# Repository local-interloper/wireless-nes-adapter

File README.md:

# Wireless NES Adapter

The goal of this project was to design a piece of hardware that you can use to play computer games 
using the original Nintendo Entertainment System controller. It comes with all the code, PCB 
schematics and information required to get a printed circuit board printed and assemble and 
program the hardware.

## Requirements

- [KiCad](https://www.kicad.org/)
- esp32-s3 devboard (make sure it looks like [this](https://docs.espressif.com/projects/esp-dev-kits/en/latest/esp32s3/_images/esp32-s3-devkitc-1-v1.1-isometric.png))
- NES Controller socket (easily found on AliExpress)
- Arduino IDE setup with [`arduino-esp32`](https://github.com/espressif/arduino-esp32) and [`ESP32-BLE-Gamepad`](https://github.com/lemmingDev/ESP32-BLE-Gamepad) installed
- A soldering iron and some solder

## How to build

1. Select a PCB printing service of your choice (I went with [Aisler](https://aisler.net/en-US)).
2. If your PCB printing service does not support native KiCad files, open `kicad/wireless-nes-adapter` 
    in KiCad and export the schematics so you can get your PCB printed.
3. Assemble the hardware.
4. With your Arduino IDE set up with the aforementioned libraries, select the ESP32-S3 as the target and flash 
    `/arduino/wireless-nes-adapter.ino` to the board.
5. Plug in your controller and power the board via USB.
6. Add the controller in your computer's bluetooth devices.

## All set!

You should now be all set. I recommend using steam as steam input allows you to use the direct input controller
you've just built as an xinput one via remapping. I recommend testing the controller on 
[Rain World](https://store.steampowered.com/app/312520/Rain_World/) or [Celeste](https://store.steampowered.com/app/504230/Celeste/) 
if you have any of those 2 titles due to their low input count requirement.

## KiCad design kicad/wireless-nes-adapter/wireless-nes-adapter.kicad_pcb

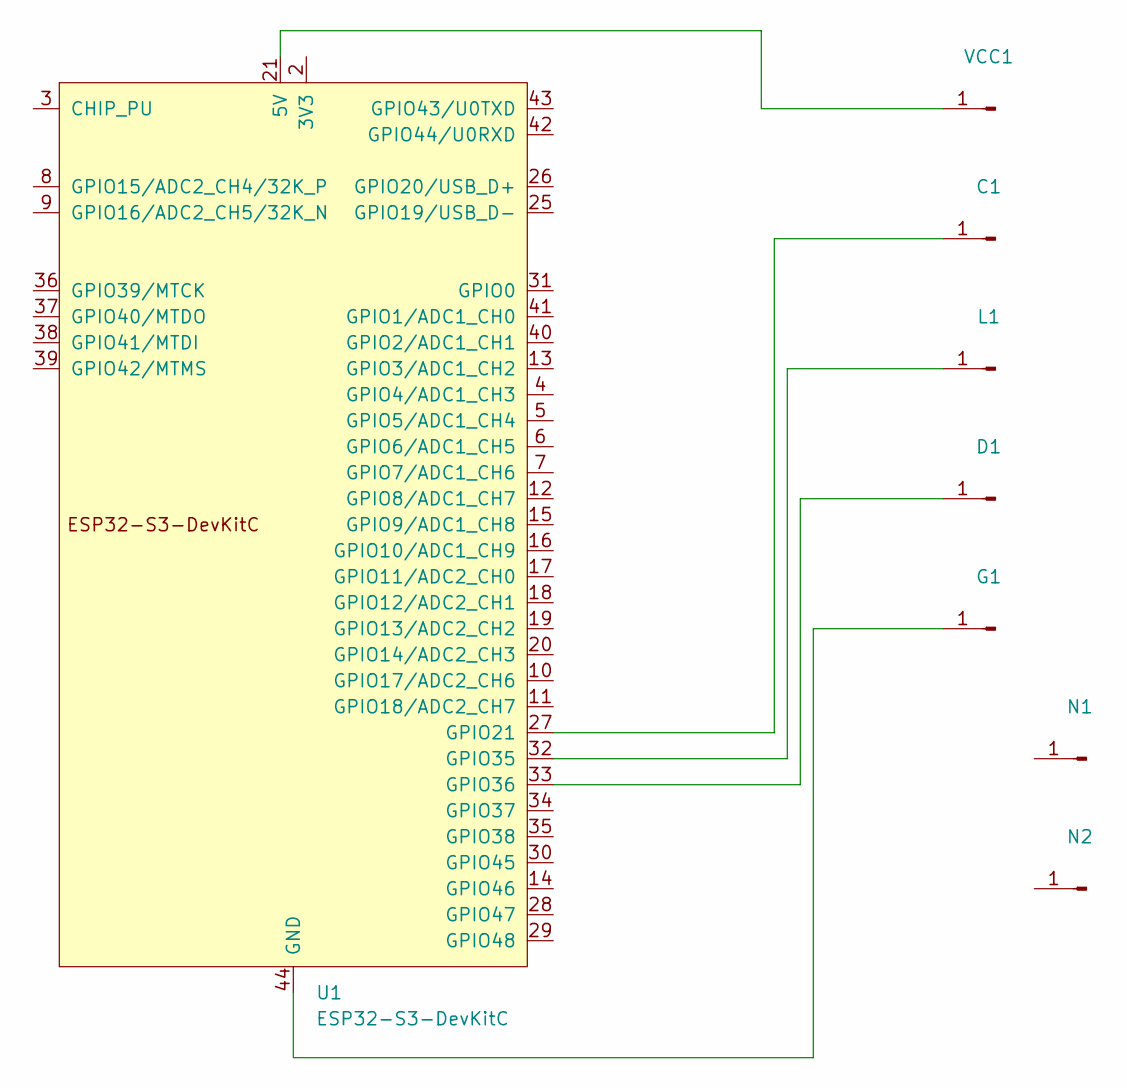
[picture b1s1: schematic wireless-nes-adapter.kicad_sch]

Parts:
C1: SolderWire-0.5sqmm_1x01_D0.9mm_OD2.1mm
D1: SolderWire-0.5sqmm_1x01_D0.9mm_OD2.1mm
G1: SolderWire-0.5sqmm_1x01_D0.9mm_OD2.1mm
L1: SolderWire-0.5sqmm_1x01_D0.9mm_OD2.1mm
N1, N2: SolderWire-0.5sqmm_1x01_D0.9mm_OD2.1mm
U1: ESP32-S3-DevKitC
VCC1: SolderWire-0.5sqmm_1x01_D0.9mm_OD2.1mm

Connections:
unnamed: C1.1, U1.27 (GPIO21)
unnamed: D1.1, U1.33 (GPIO36)
unnamed: G1.1, U1.22 (GND), U1.23 (GND), U1.24 (GND), U1.44 (GND)
unnamed: L1.1, U1.32 (GPIO35)
unnamed: U1.1 (3V3), U1.2 (3V3)
unnamed: U1.21 (5V), VCC1.1

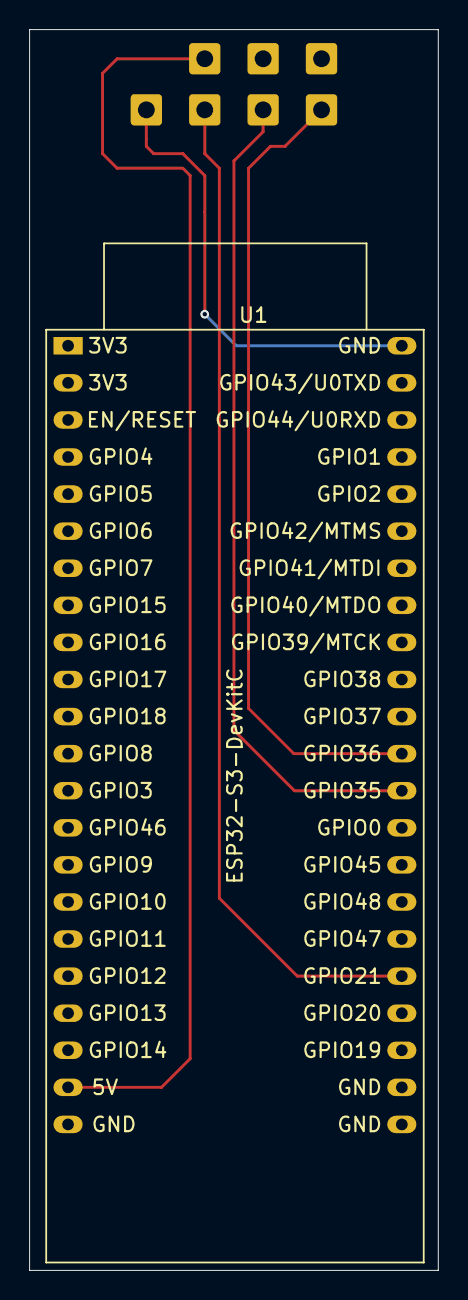
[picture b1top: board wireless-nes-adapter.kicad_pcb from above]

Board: 2 copper layers, 28.0 x 85.0 mm, 8 parts (0 on the bottom side), 6 nets.

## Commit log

2025-08-15 Init commit
2025-08-15 Added LICENSE
2025-08-15 Added the Arduino sketch
